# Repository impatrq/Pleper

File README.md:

<div align="center">

# Proyecto PLEPER
## Placa de Energía Piezoeléctrica Renovable 
<div align="center">
  
  </div>

|  |  | |
|------------|-------|-----------|
|[Página Web](https://pleper-impa.github.io/web/index.html)|pleper.infoimpa@gmail.com|[@pleper_25](https://www.instagram.com/pleper_25/?igsh=Y2xkMGg4Z2V1NHdl#)|

</div>

## ⚡ Energía en cada paso.

&nbsp;&nbsp;&nbsp;&nbsp;&nbsp;&nbsp;PLEPER es un sistema que busca aprovechar la energía mecánica generada por el paso de las personas sobre una baldosa piezoeléctrica para convertirla en energía eléctrica. Este sistema se destina a la alimentación de una luz de emergencia LED, enfocándose en su aplicación en los subtes de la Ciudad. Para optimizar su funcionamiento, el sistema cuenta con un microcontrolador que supervisa la energía generada y la muestra en una pantalla LCD, brindando información en tiempo real sobre su rendimiento.

&nbsp;&nbsp;&nbsp;&nbsp;&nbsp;&nbsp;Este proyecto busca demostrar la viabilidad de la energía piezoeléctrica, aunque el prototipo inicial se centra en aplicaciones pequeñas, la tecnología podría escalarse para aprovechar el tráfico peatonal y vehicular en entornos urbanos.

## 💡 ¿Qué aporta a la sociedad?
&nbsp;&nbsp;&nbsp;&nbsp;&nbsp;&nbsp;El mayor impacto que busca generar nuestro proyecto es el de incorporar, de manera inocua, métodos de generación de energía renovables al día a día de las personas, interactúando con la generación de energía y siendo a su vez más conscientes de las problematicas ambientales que conllevan los métodos tradiconales de generación de energía. <br>

## 🔧 Características Principales

- **Generación de Energía Limpia**: Convierte la energía mecánica del movimiento en electricidad utilizable.
- **Aplicaciones Versátiles**: Puede integrarse en pisos de estaciones de tren, centros comerciales, aeropuertos y rutas de alta circulación.
- **Bajo Impacto Ambiental**: No requiere combustibles fósiles.
- **Escalabilidad**: Diseño adaptable para aumentar la eficiencia con múltiples módulos piezoeléctricos en serie o paralelo.

## 🏙️ Aplicaciones

- **Espacios públicos**: Calles y veredas con alto tráfico peatonal.
- **Transporte**: Integración en rutas para aprovechar la presión de los vehículos.
- **Edificios Inteligentes**: Estaciones de transporte y centros comerciales.
- **Eventos Masivos**: Estadios y conciertos donde miles de personas generan energía con sus movimientos.

## 🛠️ Tecnología Utilizada

- **Componentes Principales**:
  - Sensor piezoeléctrico
  - Circuito rectificador
  - Almacenamiento en condensadores
  - Microcontrolador para medición de energía generada
  
- **Software**:
  - Diseño de placa en AutoCad
  - Simulaciones en software de circuitos

## Integrantes:
<div align="center">
  
</div>

### Victoria Josefina Baza

<br><br>

### Mauricio Blasco

<br><br>

### Víctor Raúl Broncano Ramos

<br><br>

### Ignacio García Louzan

<br><br>

### Isidro Joaquín Stabile

<br><br>
### Santiago Alejandro Tejeda

<br><br>

## Contactanos

### Instagram: [@pleper_25](https://www.instagram.com/pleper_25/)

### Pagina web: [Visitanos!](https://pleper-impa.github.io/web/index.html)

### Mail: pleper.infoimpa@gmail.com

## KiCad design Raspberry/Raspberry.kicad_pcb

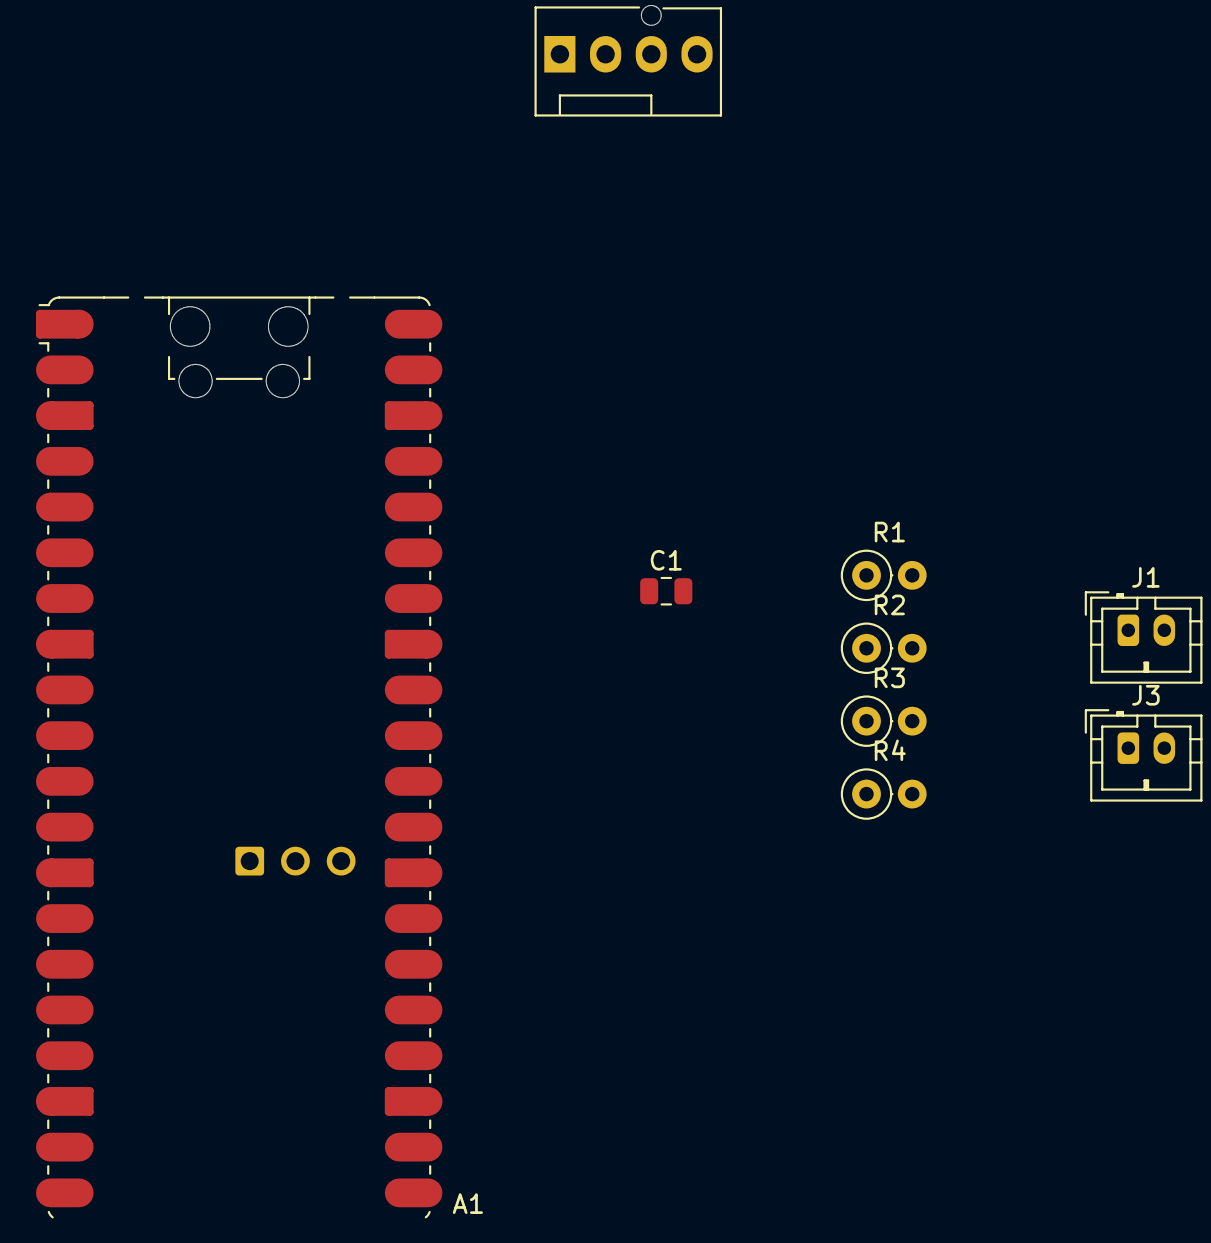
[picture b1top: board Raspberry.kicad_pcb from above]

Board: 2 copper layers, 9 parts (0 on the bottom side), 8 nets.

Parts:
A1: RaspberryPi_Pico_W; RaspberryPi_Pico_W_SMD_HandSolder
C1: 100nF; C_0805_2012Metric
J1, J3: Conn_01x02_Pin; JST_PH_B2B-PH-K_1x02_P2.00mm_Vertical
J2: Conn_01x04; FanPinHeader_1x04_P2.54mm_Vertical
R1, R2, R4: 10K; R_Axial_DIN0207_L6.3mm_D2.5mm_P2.54mm_Vertical
R3: 30K; R_Axial_DIN0207_L6.3mm_D2.5mm_P2.54mm_Vertical

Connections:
+3.3V: C1.1, J2.3
ADC0: A1.31 (GPIO26_ADC0), R3.2, R4.1
ADC1: A1.32 (GPIO27_ADC1), R1.2, R2.1
Earth: A1.3 (GND), A1.8 (GND), A1.13 (GND), A1.18 (GND), A1.23 (GND), A1.28 (GND), A1.33 (AGND), A1.38 (GND), C1.2, J1.2, J2.4, J3.2, R2.2, R4.2
GP6: A1.9 (GPIO6), J2.2
GP7: A1.10 (GPIO7), J2.1
J1: J1.1, R1.1
J3: J3.1, R3.1

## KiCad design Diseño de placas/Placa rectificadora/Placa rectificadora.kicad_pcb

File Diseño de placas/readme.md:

# Carpeta: Diseño de Placas

> Módulos electrónicos del proyecto

---

## Contenido
- `Banco de capacitores/` → Conjunto de capacitores conectados en paralelo para almacenamiento de energía.  
- `Diseño 3D/` → Modelado tridimensional del banco de capacitores y disposición general.  
- `Placa de bombeo capacitivo/` → Etapa encargada de incrementar el voltaje captado por los sensores.  
- `Placa rectificadora/` → Conversión de corriente alterna a continua para carga estable en la batería.

---

## Descripción
En esta carpeta se encuentran los **diseños electrónicos** fundamentales del sistema:  
- Implementación de **etapas de rectificación y bombeo capacitivo**.  
- Diseño del **banco de capacitores** encargado de almacenar la energía piezoeléctrica.  
- Integración entre módulos para alimentar el sistema de medición y visualización.  

---

## Herramientas utilizadas
- **KiCad** para diseño de PCBs.  
- **PDFGear** para visualización e impresión.
---

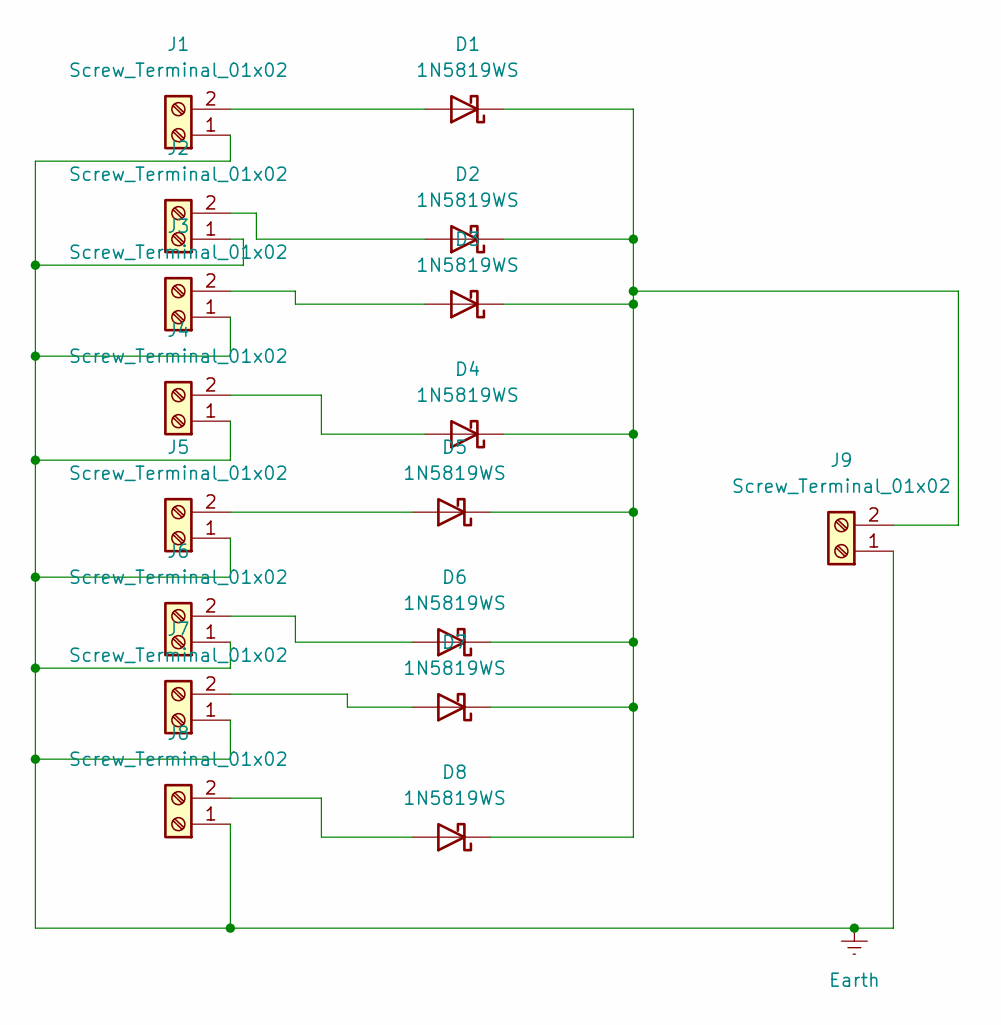
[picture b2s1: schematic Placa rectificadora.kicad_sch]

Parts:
D1, D2, D3, D4, D5, D6, D7, D8: 1N5819WS; D_DO-41_SOD81_P10.16mm_Horizontal
J1, J2, J3, J4, J5, J6, J7, J8, J9: Screw_Terminal_01x02; TerminalBlock_Altech_AK300-2_P5.00mm

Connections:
Earth: J1.1, J2.1, J3.1, J4.1, J5.1, J6.1, J7.1, J8.1, J9.1
unnamed: D1.2 (A), J1.2
unnamed: D1.1 (K), D2.1 (K), D3.1 (K), D4.1 (K), D5.1 (K), D6.1 (K), D7.1 (K), D8.1 (K), J9.2
unnamed: D2.2 (A), J2.2
unnamed: D3.2 (A), J3.2
unnamed: D4.2 (A), J4.2
unnamed: D5.2 (A), J5.2
unnamed: D6.2 (A), J6.2
unnamed: D7.2 (A), J7.2
unnamed: D8.2 (A), J8.2

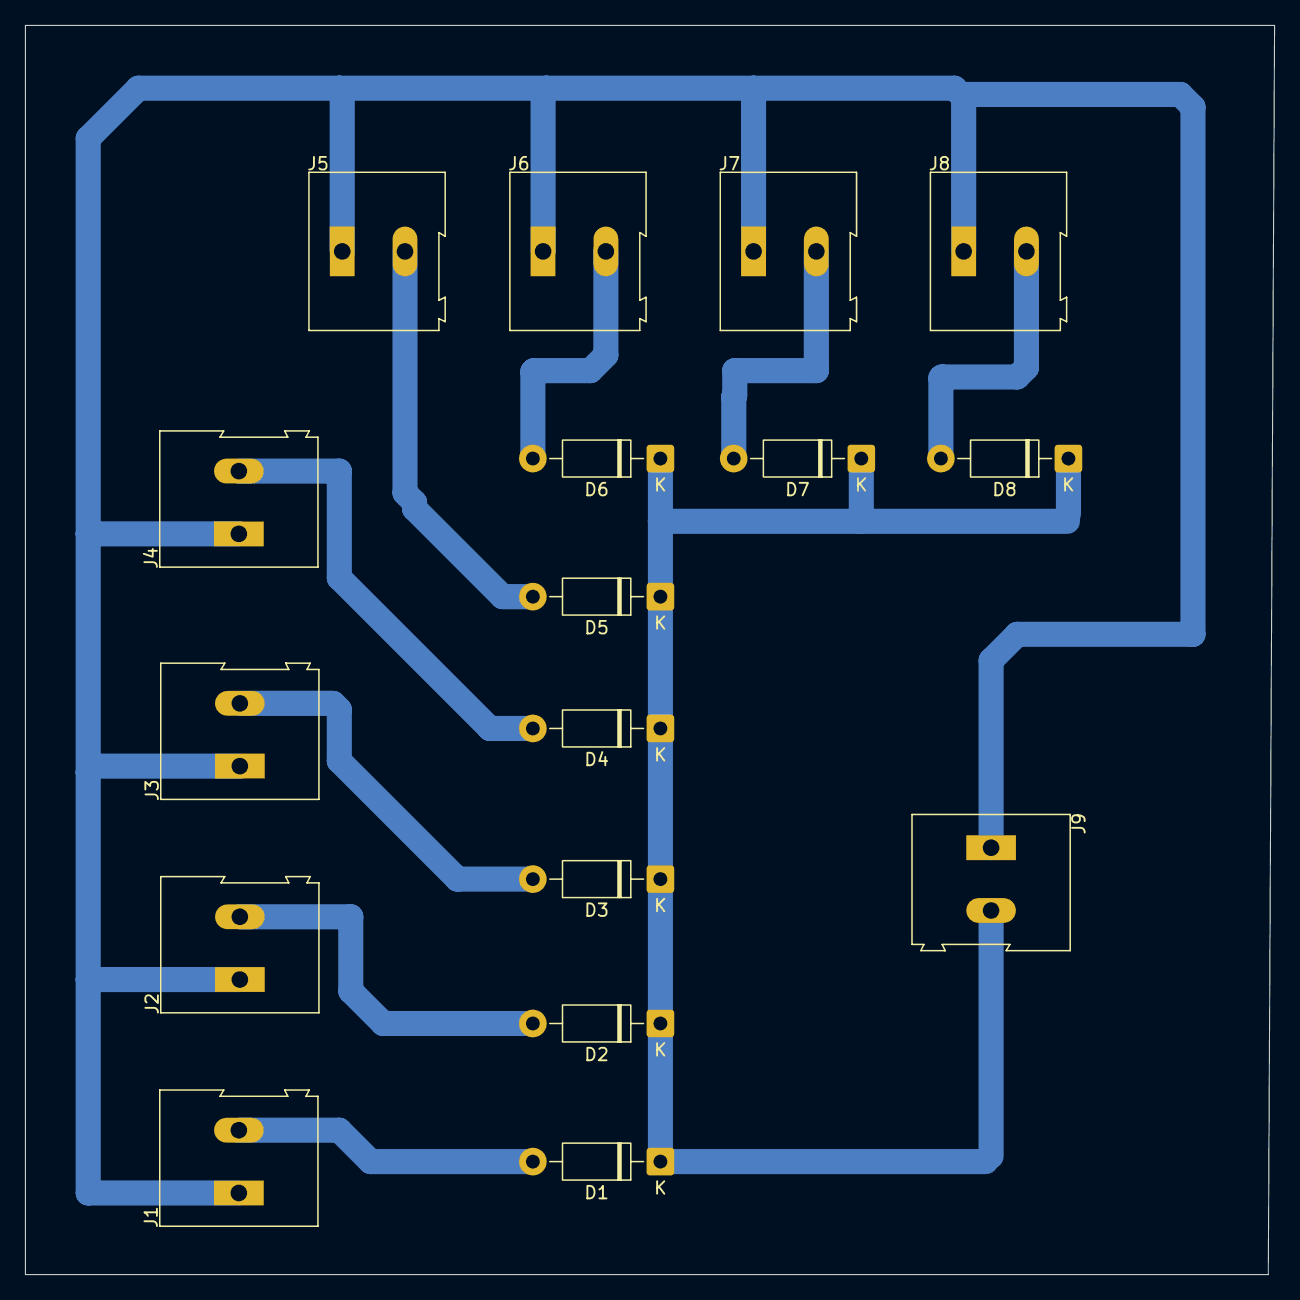
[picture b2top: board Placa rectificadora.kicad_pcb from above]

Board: 2 copper layers, 99.5 x 99.5 mm, 17 parts (0 on the bottom side), 10 nets.

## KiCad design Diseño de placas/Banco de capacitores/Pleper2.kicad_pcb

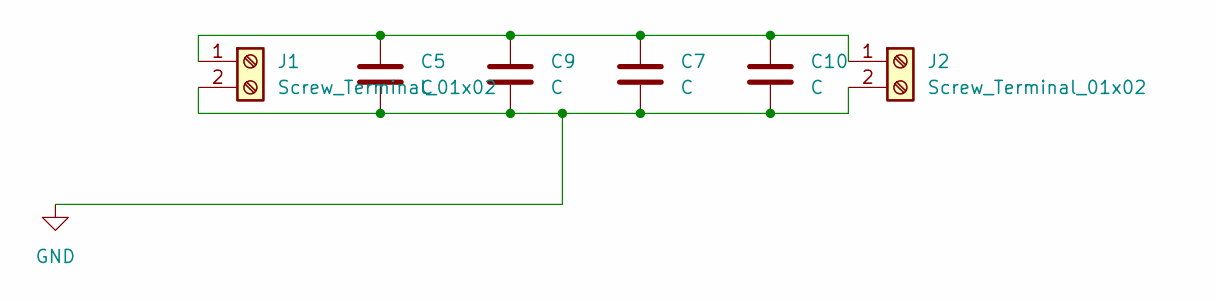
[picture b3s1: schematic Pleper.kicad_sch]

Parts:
C5, C7, C9, C10: C; CP_Radial_D30.0mm_P10.00mm_SnapIn
J1, J2: Screw_Terminal_01x02; TerminalBlock_Altech_AK300-2_P5.00mm

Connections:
GND: C5.2, C7.2, C9.2, C10.2, J1.2, J2.2
unnamed: C5.1, C7.1, C9.1, C10.1, J1.1, J2.1

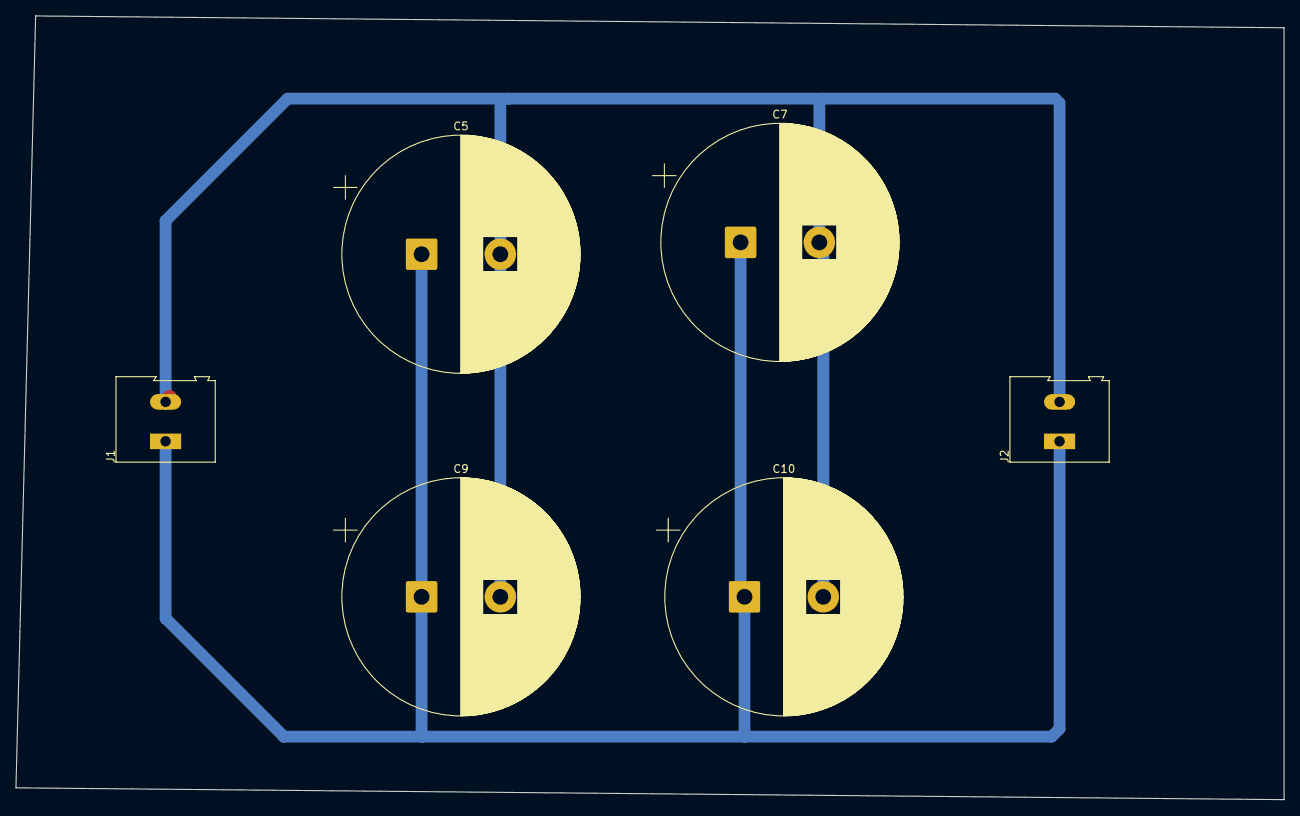
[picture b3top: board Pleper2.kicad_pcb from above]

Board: 2 copper layers, 161.0 x 99.5 mm, 6 parts (0 on the bottom side), 2 nets.

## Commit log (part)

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2025-09-24 -link pagina web
2025-09-24 Añado el banner del proyecto
2025-09-24 Añado banner en pdf
2025-09-24 Pisada epica en el prototipo de la placa
2025-09-24 Agrego fotos del desarrollo del proyecto
2025-09-24 Añado archivo pdf del pcb del banco de capacitores
2025-09-24 Añado archivo de Kicad Placa rectificadora
2025-09-24 Añado carpeta con material de referencia
2025-09-24 Subo material de referencia
2025-09-26 Subo carpeta con los modelos 3D
2025-09-26 Subo vista del diseño 3D de la placa rectificadora
2025-09-26 Subo archivo stl del banco de capacitores
2025-09-26 Subo vista del diseño 3D del banco de capacitores
2025-09-26 Agrego imagenes
2025-10-08 Add files via upload
    Subir foto del boceto de la placas
2025-10-08 Add files via upload
    no estoy farmeand commits... lo escribí mal
2025-10-08 Add files via upload
    dibujo muuuy boceto de la rectificadora en.... paint.
2025-10-08 foto del boceto simulado
2025-10-08 Lo moví a su respectiva carpeta
    en la carpeta de la placa
2025-10-08 Subo fotos del circuito del banco
2025-10-08 Actualizo carpeta técnica
2025-10-17 Medición con un tope en cada esquina
2025-10-17 Medición con un tope en un grupo
2025-10-17 Medición con dos topes en un grupo
2025-10-17 Medición con 3 topes en un grupo
2025-10-17 Medición con 4 topes en un grupo
2025-10-17 Reubico Estructura AutoCAD/Vista Isometrica.png
2025-10-17 Reubico Estructura AutoCAD/Vista Perfil.png
2025-10-17 Reubico Estructura AutoCAD/placa pleper prototipo.dwg
2025-10-17 Creo carpeta de AutoCad
2025-10-17 Creo carpeta de canva
2025-10-17 Creo carpeta de imágenes de AutoCad
2025-10-17 Creo Archivos de AutoCad
2025-10-17 Reubico el archivo
2025-10-17 Vista Perfil
2025-10-17 Canva de prototipo uno de topes
2025-10-17 Primer Prototipo AutoCad
2025-10-17 Segundo Prototipo Pleper
2025-10-17 Primer Prototipo de tope para la placa
2025-10-17 Medición de grupo de con un tope en cada esquina
2025-10-17 Create fotos
2025-10-17 Creo la carpeta de la Placa rectificadora
2025-10-17 Borro el archivo de foto
2025-10-17 Borro el archivo de fotos
2025-10-17 Creo el archivo fotos
2025-10-17 Creo la carpeta banco de capacitores correctamente
2025-10-17 Creo la carpeta de la publicación triple
2025-10-17 Publicación banco de capacitores
2025-10-17 Video base del banco de capacitores
2025-10-17 Publicación de la placa rectificadora
2025-10-17 Video base placa rectificadora
2025-10-17 Video placa rectificadora
2025-10-17 Portada triple de instagram inicial
2025-10-17 Portada triple final
2025-10-17 portada almacenamiento
2025-10-17 Portada estructura
2025-10-22 Creo reporte de avances de Agosto
2025-10-22 Adjunto el Banner del proyecto en formato JPG
2025-10-23 Creo reporte de avances de Octubre
2025-10-23 Creo bitácora de Agosto
2025-10-23 puse mi nombre en la bitacora
2025-10-23 Creo reporte de avances Septiembre
2025-10-23 Corrijo semanas de Septiembre
2025-10-23 corregi dias de la semana 1 de octubre
2025-10-23 corregi semana 2 de octubre
2025-10-23 corrigo los dias del mes de octurbe para que coincidan
2025-10-23 agregue mi bitácora semana 4 de octubre
2025-10-23 Agregué mi avance de la semana 3 de octubre
2025-10-23 Agregué mi avance de "Semana 1 y 2 de Octubre"
2025-10-23 corregí faltas ortograficas
2025-10-23 Subo el banner actualizado con la imagen circular
2025-10-23 Subo el banner con la imagen cuadrada
2025-10-23 Subo el banner final del proyecto
2025-10-23 Borro banner antiguo
2025-10-24 Actualización de semana 4 octubre
2025-10-24 subo mi avance de la semana 1 septiembre
2025-10-27 Actualizo semana del 20 al 24
2025-10-27 Actualizo la semana del 6 al 10
2025-10-27 Actualizo la semana del 29 al 3
2025-10-27 Arreglo los nombres en la bitacora
2025-10-27 Actualizo la semana del 22 al 26
2025-10-27 Actualizo la semana del 15
2025-10-27 Actualizo la semana del 15 al 19
2025-10-28 Semana 15-19 Septiembre
2025-10-28 codigo de pleper
    commit de .vscode en el codigo de pleper
2025-10-28 codigo pleper
    codigo de pleper actualizado
2025-10-28 pagina web
    actualizacion de la pagina web
2025-10-28 Creo manual de Usuario y actualizo carpeta técnica
2025-10-28 Actualizo manual de usuario
2025-10-28 Actualizar bitácora de octubre con avances del proyecto
    Se actualizó la bitácora de octubre con detalles sobre el progreso de los integrantes del proyecto, incluyendo investigaciones sobre circuitos, mediciones de pulsos y avances en el código.
2025-10-28 Actualización Manual de Usuario
2025-10-28 Subo la introducción del video
2025-10-28 Actualizo el guion
2025-10-28 Subo actualización de Manual de usuario
2025-10-28 Semana 4 - 8 Agosto
2025-10-28 Actualización del guion del video
2025-10-28 Semana 11 - 15 Agosto
2025-10-28 Semana 18 - 22 Agosto
2025-10-28 Corrección de espacios Octubre
2025-10-28 Actualizo el guion para el video
2025-10-28 Prototipo de la placa de carga
2025-10-28 Investigación del circuito
2025-10-28 carpeta de boceto
2025-10-29 Añado video de resortes y topes impresos
2025-10-29 video bases de caucho y sensores piezoelectricos
2025-10-29 edit pagina web
    mejora en la seccion de sponsors
2025-10-29 style.cc
    agrego style
2025-10-29 sitemap
    sitemap agregado
2025-10-29 reusmen html
    resumen html agregado
2025-10-29 html game
    .
2025-10-29 agrego .js
    .
2025-10-29 html de introduccion
    .
2025-10-29 integrantes.css
    .
2025-10-29 index.html
2025-10-29 html sitemap
    .
2025-10-29 formulario.html
    .
2025-10-29 descripcion.html
    .
2025-10-29 back to top.js
    .
2025-10-29 imagenes para la página
    .
2025-10-29 .vs
    .
2025-10-29 Corrección
2025-10-29 KiCad del Circuito
2025-10-29 Creo readme para la carpeta de AutoCad
2025-10-29 eliminacion de la carpeta de imagenes
    para poder agregar una carpeta de imagenes mas completa
2025-10-29 video de explicacion del proyecto
2025-10-29 sponsor 5 cooperadora impa
    .
2025-10-29 sponsor 4 Newton
    .
2025-10-29 sponsor 3 Autogoma Bernal
    .
2025-10-29 sponsor 1 resortes avellaneda
    .
2025-10-29 sponsor 2 elemon
    .
2025-10-29 gif de la piezoelectricidad
    .
2025-10-29 fondo del html de resumen
2025-10-29 fondo de index.html
    .
2025-10-29 paul langevin
    .
2025-10-29 mundo actual
    .
2025-10-29 materiales piezoelectricos
    .
2025-10-29 libro de piezoelectricidad
    .
2025-10-29 fondo de introduccion.html
2025-10-29 foto de integrantes.html
    .
2025-10-29 estados unidos y japon (historia de la piezoelectricidad)
    .
2025-10-29 Actualizo readme del Diseño de Placas
2025-10-29 ejemplos piezoelectricos en la historia
    .
2025-10-29 fondo descripcion.html
    .
2025-10-29 hermanos curie (historia de la piezoelectricidad)
    .
2025-10-29 material historico de la piezoelectricidad
    .
2025-10-29 Corrijo nombres de carpeta de diseño 3D
2025-10-29 Prototipo del cicuito de carga por bombeo de capacitores
2025-10-29 Video publicación explicacion de pleper
2025-10-29 Video editado en canva
2025-10-29 Creo readme en la carpeta de Docs del Proyecto
2025-10-29 Pegado de los cables con silicona
2025-10-29 Resoldado de los pines de la Raspberry Pi W
2025-10-29 Resoldado de los piezoeléctricos despegados
2025-10-29 Prueba de funcionamiento del banco de capacitores
2025-10-29 Pegado de los topes de goma a los piezoeléctricos
2025-10-29 video recorte de caucho
2025-10-29 Creo readme de la carpeta de Imágenes Proyecto
2025-10-29 video soldando los sensores
2025-10-29 Video de la publicación
2025-10-29 Video probando los sensores piezoeléctricos
2025-10-29 Sigan su bitacora de la semana 4 - 8
2025-10-29 Sigan su bitacora semana 11 - 15
2025-10-29 Sigan su bitaoora 18 - 22
2025-10-29 Sigan su bitacora 25 - 29
2025-10-29 bitacora personal 1era semana de Agosto.md
2025-10-29 Bitácora personal 2da semana de Agosto.md
2025-10-29 Bitácora personal 3era semana Agosto.md
2025-10-29 1era semana de agosto
2025-10-29 2da semana agosto
2025-10-29 3era semana de agosto
2025-10-29 4to semana de agosto
2025-10-29 Correccion 1era semana de agosto
    Updated project log for September with detailed contributions from team members.
2025-10-29 1era semana de septiembre
2025-10-29 2da semana de septiembre
    Added detailed progress notes for the project structure and design considerations over multiple weeks.
2025-10-29 4ta semana de septiembre
    Added details about Victor Raul Broncano's tasks related to the copper plate and capacitor bank connections.
2025-10-29 1er semana de octubre
2025-10-29 2da semana de octubre
    Added updates from team members regarding project progress and challenges faced during the week.
2025-10-29 3er semana de octubre
2025-10-29 4ta semana de octubre
    Added updates from team members regarding project progress, including measurements, component purchases, and coding challenges.
2025-10-29 Actualizo guion
2025-10-30 Reparto del guion del video
2025-10-30 Corrijo errores en los archivos
2025-10-30 Actualizo el guion de video para fotos
2025-10-30 Creo bitácora de abril
2025-10-30 Actualizo del 4 al 8
    Added entry for Mauricio Blasco's work on Instagram publication.
2025-10-30 Actualizo del 14 al 18
    Added a note about project research on piezoelectricity.
2025-10-30 actualizo del 21 al 25
2025-10-30 actualizo semana 25 al 29
2025-10-30 Semana 11 a 15
2025-10-30 Semana del 18 al 22
    Added information about spring measurements and contact with Resortecnica for assistance.
2025-10-30 Borro bitácora equivocada
2025-10-30 Actualizo los roles en el guion
2025-10-30 Actualizo imagen del proyecto
2025-10-30 Subo imagen de la impresión de los topes
2025-10-30 Creo carpeta de placas
2025-10-30 Creo la carpeta de tareas manuales
2025-10-30 Creo carpeta mediciones
2025-10-30 Creo carpeta de componentes
2025-10-30 Reubico imagen del logo
2025-10-30 Reacomodo las ultimas imágenes sueltas
2025-10-30 Subo diseño final de la baldosa
2025-10-30 Subo capturas del modelo de la placa
2025-10-30 Arreglo readme
2025-10-31 Actualizo modelos 3D
2025-10-31 Actualización
2025-11-01 Subo manual de usuario .pdf
2025-11-04 Actualizo readme
2025-11-05 subo video para la presentacion
2025-11-05 Subo video para el video
2025-11-05 Subo datasheet del ltc 3588
2025-11-05 Subo los objetivos planteado a principio de año
2025-11-05 Borro archivo del manual de usuario corrupto
2025-11-05 Subo diseños de placa
2025-11-05 Subo fotos grupales
2025-11-05 Acomodo el logo
2025-11-06 Actualización logo
2025-11-06 Agrego foto grupal en el readme
2025-11-06 Actualizo foto
2025-11-06 Actualización de bitacora
2025-11-06 Subi el DWG del Pilar
2025-11-06 Subo Circulo de Tope Resorte
2025-11-06 Subo STL del Pilar/Circulo
2025-11-08 Actualizo otra vez carpeta técnica
    (ayuda mañana rindo el parcial de la unlp)
2025-11-08 Otra actualización de la Carpeta Técnica
2025-11-08 Actualizo carpeta técnica y añado la versión pdf
2025-11-08 Subo Carpeta de Campo
2025-11-08 Add Ultimaker Cura to tools list
2025-11-08 Corrijo readme
2025-11-10 Actualizo semana 5 de Octubre
2025-11-10 Actualizo la cuarta semana de la bitácora
2025-11-10 Actualizacion
2025-11-10 Saque la placa que no se terminó haciendo
2025-11-10 Actualizo Carpeta de Campo
2025-11-11 Actualizaciones carpeta de campo
2025-11-12 subo autocad de la carcasa de la placa rectificadora
2025-11-12 Subo el STL de la carcasa de la placa rectificadora
2025-11-12 Publicació de la Feria
2025-11-12 Creo carpeta para CVs
2025-11-12 Actualizo readme de la carpeta de cvs
2025-11-12 Subo mi CV a los documentos
2025-11-12 Subo folleto final del proyecto par ala muestra
2025-11-12 Elimino folletos anteriores
2025-11-12 Subo diseño de las remeras realizado en canva
2025-11-12 Actualizo la semana del 3 al 7
2025-11-12 Actualizo la semana del 10 al 15
2025-11-12 Actualizo la semana del 27 al 31
2025-11-12 Creo la bitácora de Julio
2025-11-12 Actualizo julio
2025-11-12 Actualización de carpeta de campo
2025-11-12 Creación de pdf de la carpeta de campo
2025-11-12 Actualizo readme para que coincida con los últimos arreglos
2025-11-12 Reordeno algunos documentos
2025-11-12 Actualizo el readme para que coincida con los cambios
2025-11-12 Adjunto mi curriculum
2025-11-12 Corrijo formato
2025-11-12 Actualizo carpeta de campo y subo el pdf
2025-11-13 Actualizo CV y Planilla de Compras
2025-11-13 Actualizo cambios en la Carpeta Técnica y el Manual de Usuario
